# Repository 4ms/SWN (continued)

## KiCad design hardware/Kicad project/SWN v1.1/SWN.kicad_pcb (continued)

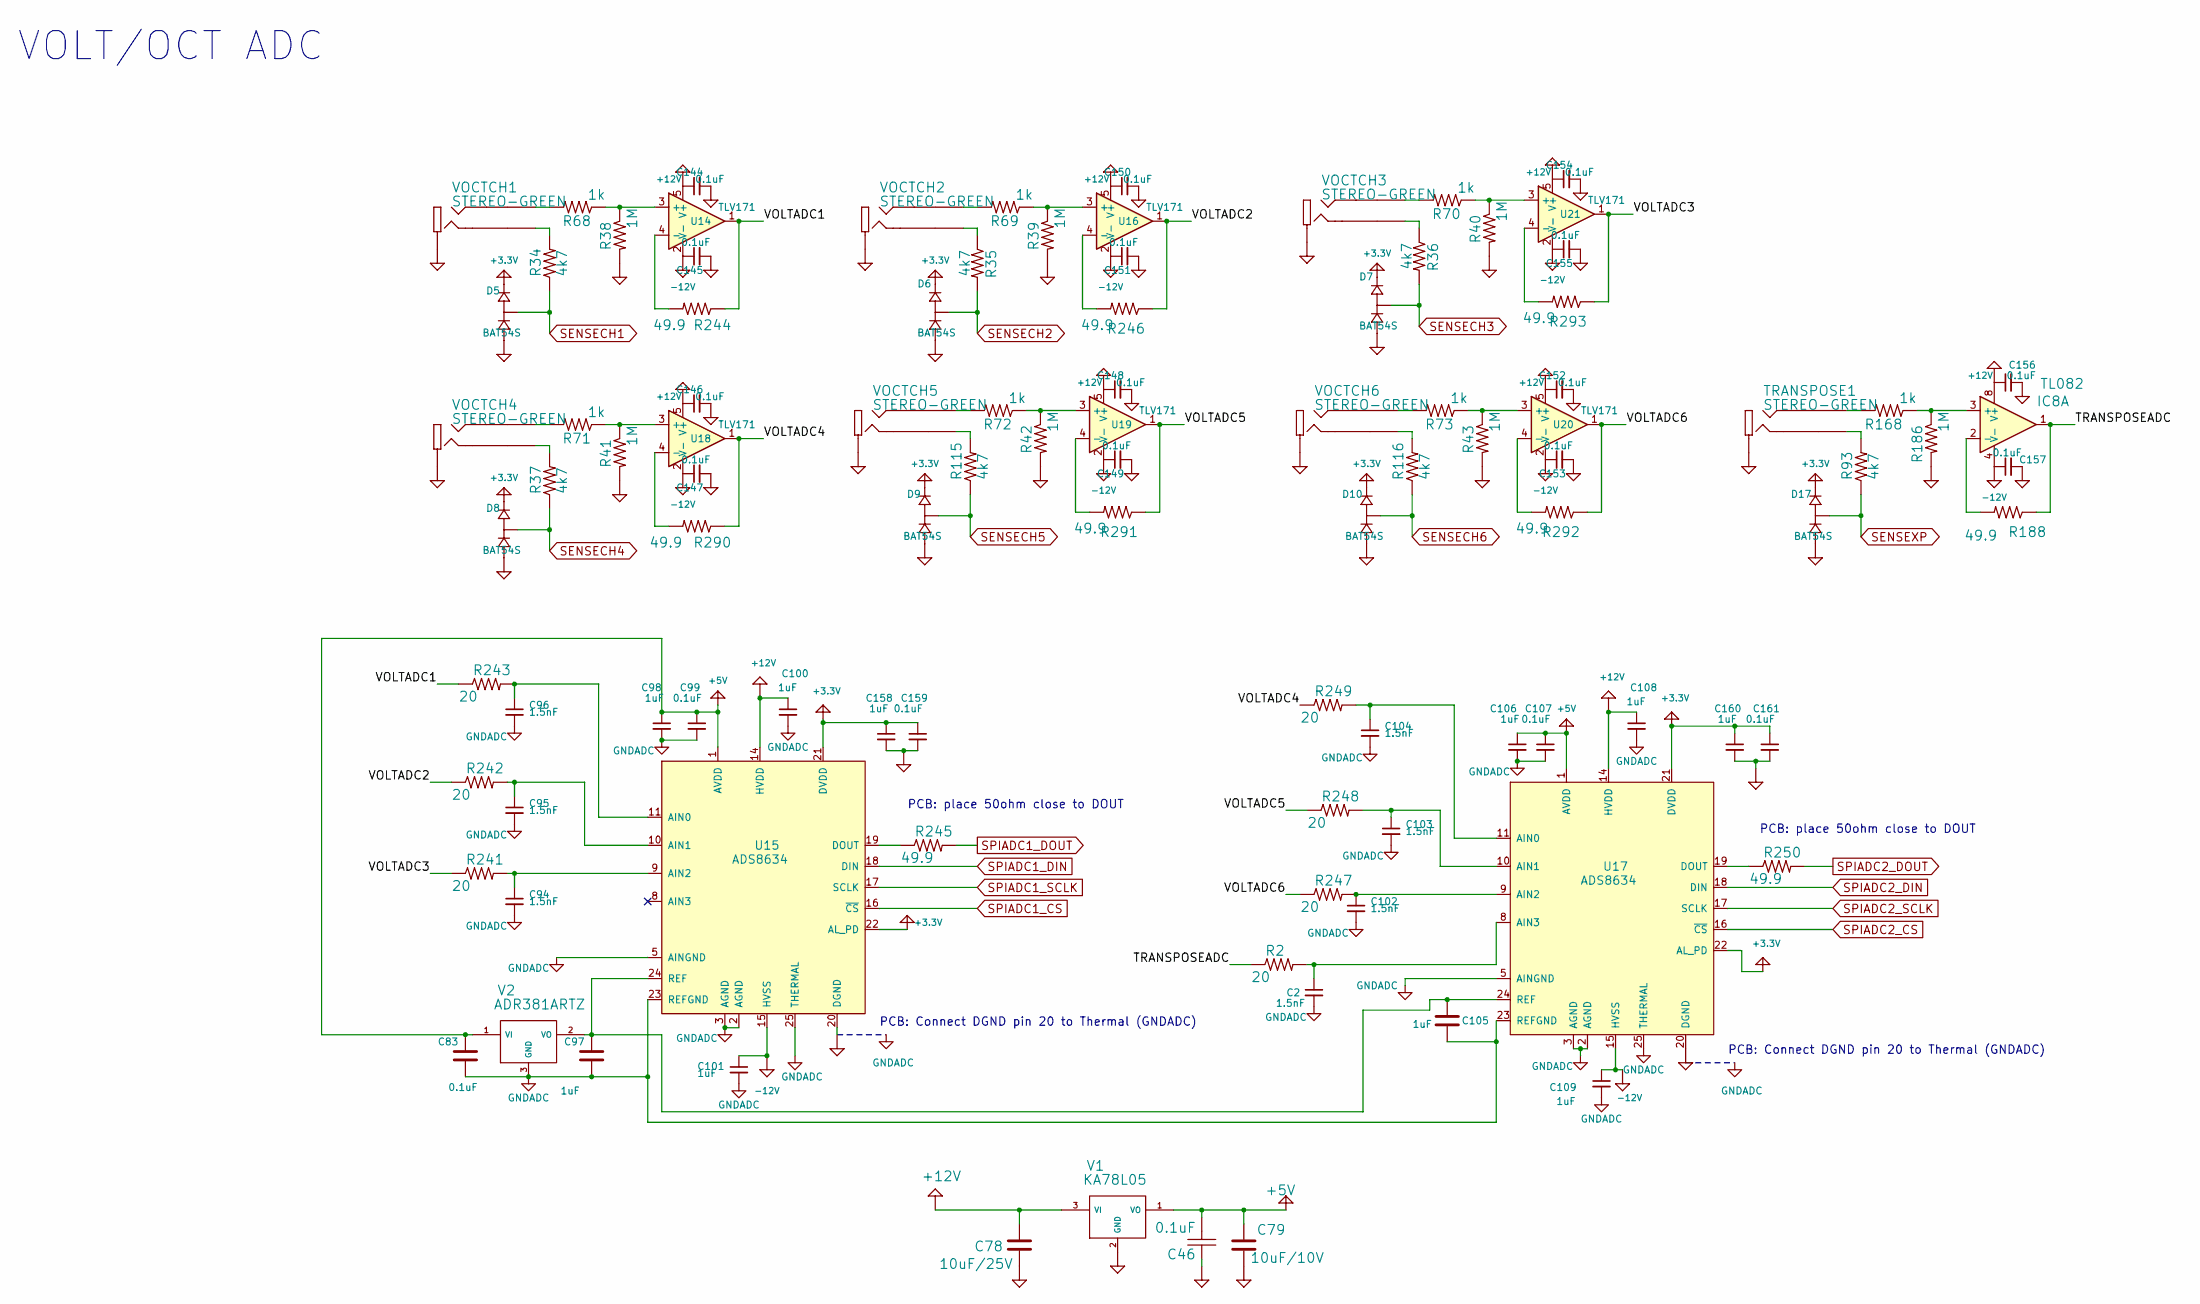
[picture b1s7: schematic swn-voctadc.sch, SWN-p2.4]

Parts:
C2, C94, C95, C96, C102, C103, C104: 1.5nF; C0603
C46, C83, C99, C107, C144, C145, C146, C147, C148, C149, C150, C151, C152, C153, C154, C155, C156, C157, C159, C161: 0.1uF; C0603
C78: 10uF/25V; C1206
C79: 10uF/10V; C0603
C97, C98, C100, C101, C105, C106, C108, C109, C158, C160: 1uF; C0603
D5, D6, D7, D8, D9, D10, D17: BAT54S; SOT23
IC8: TL082; TSSOP-8_4.4x3mm_Pitch0.65mm
R2, R241, R242, R243, R247, R248, R249: 20; R0603
R34, R35, R36, R37, R93, R115, R116: 4k7; R0603
R38, R39, R40, R41, R42, R43, R186: 1M; R0603
R68, R69, R70, R71, R72, R73, R168: 1k; R0603
R188, R244, R245, R246, R250, R290, R291, R292, R293: 49.9; R0603
TRANSPOSE1: STEREO-GREEN; PJ301M-12
U14, U16, U18, U19, U20, U21: TLV171; SOT-23-5
U15, U17: ADS8634; QFN-24-1EP_4x4mm_Pitch0.5mm
V1: KA78L05; SOT-89-3
V2: ADR381ARTZ; SOT23-3_PO132
VOCTCH1, VOCTCH2, VOCTCH3, VOCTCH4, VOCTCH5, VOCTCH6: STEREO-GREEN; PJ301M-12

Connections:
+3.3V: C158.1, C159.1, C160.1, C161.1, D5.2 (CATHODE), D6.2 (CATHODE), D7.2 (CATHODE), D8.2 (CATHODE), D9.2 (CATHODE), D10.2 (CATHODE), D17.2 (CATHODE), U15.21 (DVDD), U15.22 (AL_PD), U17.21 (DVDD), U17.22 (AL_PD); also elsewhere on the board
+5V: C46.2, C79.2, C83.1, C98.1, C99.1, C106.1, C107.1, U15.1 (AVDD), U17.1 (AVDD), V1.1 (VO), V2.1 (VI)
+12V: C78.1, C100.1, C108.1, C144.1, C146.1, C148.1, C150.1, C152.1, C154.1, C156.1, IC8.8 (V+), U14.5 (V+), U15.14 (HVDD), U16.5 (V+), U17.14 (HVDD), U18.5 (V+), U19.5 (V+), U20.5 (V+), U21.5 (V+), V1.3 (VI); also elsewhere on the board
-12V: C101.1, C109.1, C145.1, C147.1, C149.1, C151.1, C153.1, C155.1, C157.1, IC8.4 (V-), U14.2 (V-), U15.15 (HVSS), U16.2 (V-), U17.15 (HVSS), U18.2 (V-), U19.2 (V-), U20.2 (V-), U21.2 (V-); also elsewhere on the board
/V/OCT ADC/TRANSPOSEADC: IC8.1, R2.1, R188.1
/V/OCT ADC/VOLTADC1: R243.1, R244.1, U14.1
/V/OCT ADC/VOLTADC2: R242.1, R246.1, U16.1
/V/OCT ADC/VOLTADC3: R241.1, R293.1, U21.1
/V/OCT ADC/VOLTADC4: R249.1, R290.1, U18.1
/V/OCT ADC/VOLTADC5: R248.1, R291.1, U19.1
/V/OCT ADC/VOLTADC6: R247.1, R292.1, U20.1
GNDADC: C2.2, C83.2, C94.2, C95.2, C96.2, C97.2, C98.2, C99.2, C100.2, C101.2, C102.2, C103.2, C104.2, C105.2, C106.2, C107.2, C108.2, C109.2, U15.2 (AGND), U15.3 (AGND), U15.5 (AINGND), U15.23 (REFGND), U15.25 (THERMAL), U17.2 (AGND), U17.3 (AGND), U17.5 (AINGND), U17.23 (REFGND), U17.25 (THERMAL), V2.3 (GND); also elsewhere on the board
unnamed: C2.1, R2.2, U17.8 (AIN3)
unnamed: C94.1, R241.2, U15.9 (AIN2)
unnamed: C95.1, R242.2, U15.10 (AIN1)
unnamed: C96.1, R243.2, U15.11 (AIN0)
unnamed: C102.1, R247.2, U17.9 (AIN2)
unnamed: C103.1, R248.2, U17.10 (AIN1)
unnamed: C104.1, R249.2, U17.11 (AIN0)
unnamed: C97.1, C105.1, U15.24 (REF), U17.24 (REF), V2.2 (VO)
unnamed: IC8.2 (-), R188.2
unnamed: IC8.3 (+), R168.1, R186.1
unnamed: R34.2, VOCTCH1.3 (TIP-SW)
unnamed: R35.1, VOCTCH2.3 (TIP-SW)
unnamed: R36.1, VOCTCH3.3 (TIP-SW)
unnamed: R37.2, VOCTCH4.3 (TIP-SW)
unnamed: R38.1, R68.1, U14.3 (+)
unnamed: R39.1, R69.1, U16.3 (+)
unnamed: R40.1, R70.1, U21.3 (+)
unnamed: R41.1, R71.1, U18.3 (+)
unnamed: R42.1, R72.1, U19.3 (+)
unnamed: R43.1, R73.1, U20.3 (+)
unnamed: R68.2, VOCTCH1.1 (TIP)
unnamed: R69.2, VOCTCH2.1 (TIP)
unnamed: R70.2, VOCTCH3.1 (TIP)
unnamed: R71.2, VOCTCH4.1 (TIP)
unnamed: R72.2, VOCTCH5.1 (TIP)
unnamed: R73.2, VOCTCH6.1 (TIP)
unnamed: R93.2, TRANSPOSE1.3 (TIP-SW)
unnamed: R115.2, VOCTCH5.3 (TIP-SW)
unnamed: R116.2, VOCTCH6.3 (TIP-SW)
unnamed: R168.2, TRANSPOSE1.1 (TIP)
unnamed: R244.2, U14.4 (-)
unnamed: R245.1, U15.19 (DOUT)
unnamed: R246.2, U16.4 (-)
unnamed: R250.1, U17.19 (DOUT)
unnamed: R290.2, U18.4 (-)
unnamed: R291.2, U19.4 (-)
unnamed: R292.2, U20.4 (-)
unnamed: R293.2, U21.4 (-)
SENSECH1: D5.3 (COMMON), R34.1; also elsewhere on the board
SENSECH2: D6.3 (COMMON), R35.2; also elsewhere on the board
SENSECH3: D7.3 (COMMON), R36.2; also elsewhere on the board
SENSECH4: D8.3 (COMMON), R37.1; also elsewhere on the board
SENSECH5: D9.3 (COMMON), R115.1; also elsewhere on the board
SENSECH6: D10.3 (COMMON), R116.1; also elsewhere on the board
SENSEXP: D17.3 (COMMON), R93.1; also elsewhere on the board
SPIADC1_CS: U15.16 (~CS); also elsewhere on the board
SPIADC1_DIN: U15.18 (DIN); also elsewhere on the board
SPIADC1_DOUT: R245.2; also elsewhere on the board
SPIADC1_SCLK: U15.17 (SCLK); also elsewhere on the board
SPIADC2_CS: U17.16 (~CS); also elsewhere on the board
SPIADC2_DIN: U17.18 (DIN); also elsewhere on the board
SPIADC2_DOUT: R250.2; also elsewhere on the board
SPIADC2_SCLK: U17.17 (SCLK); also elsewhere on the board

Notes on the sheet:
VOLT/OCT ADC
PCB: place 50ohm close to DOUT
PCB: Connect DGND pin 20 to Thermal (GNDADC)

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
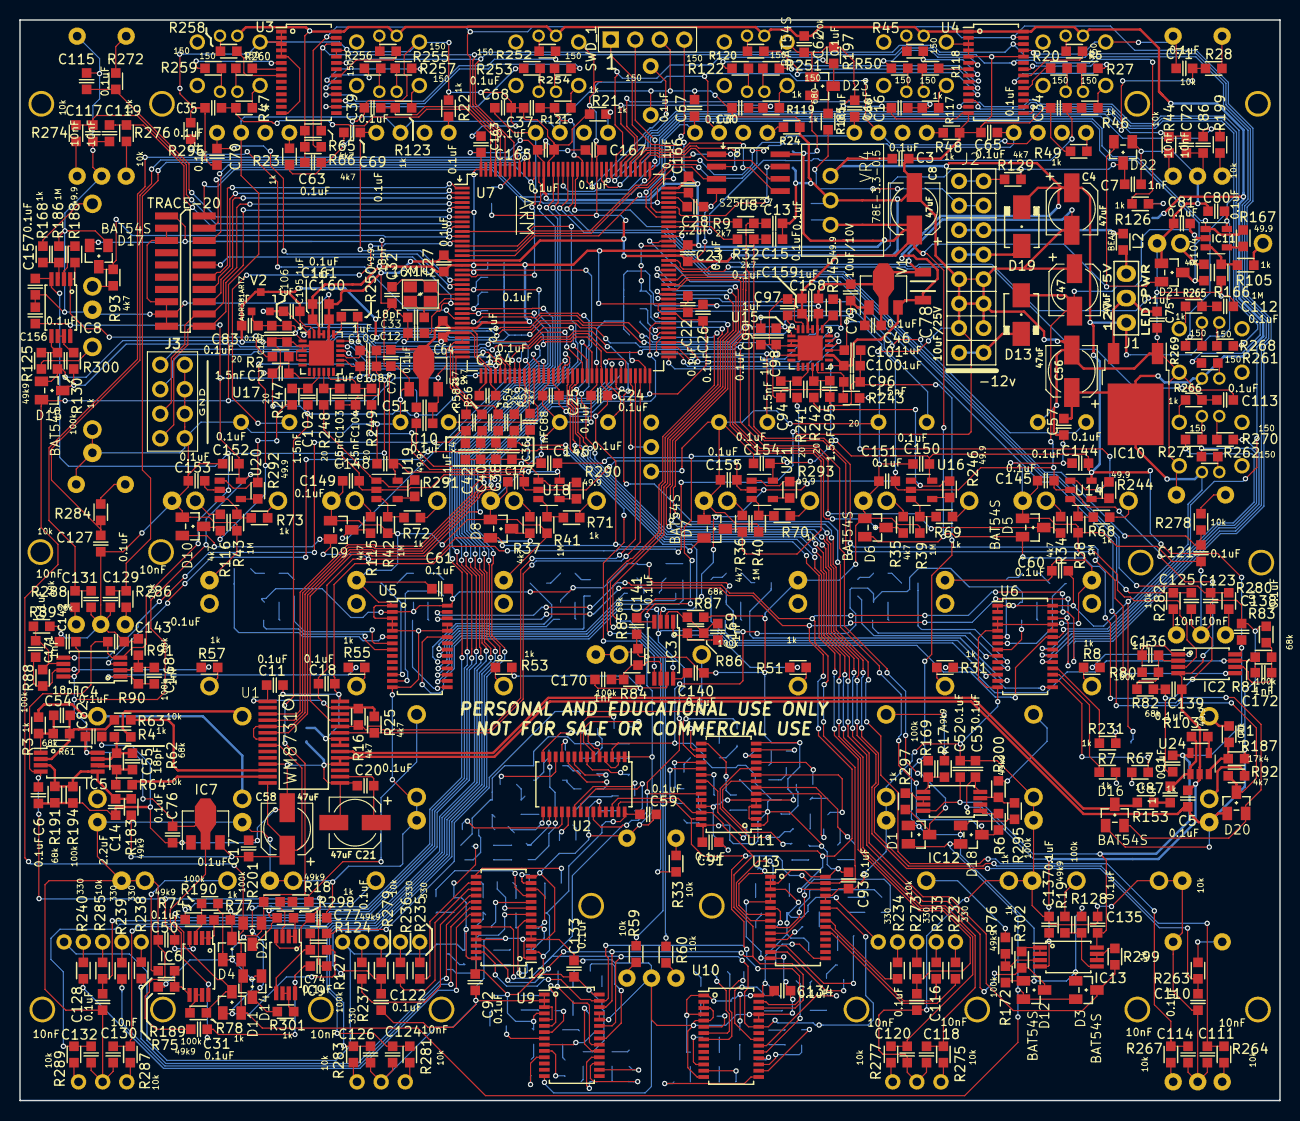
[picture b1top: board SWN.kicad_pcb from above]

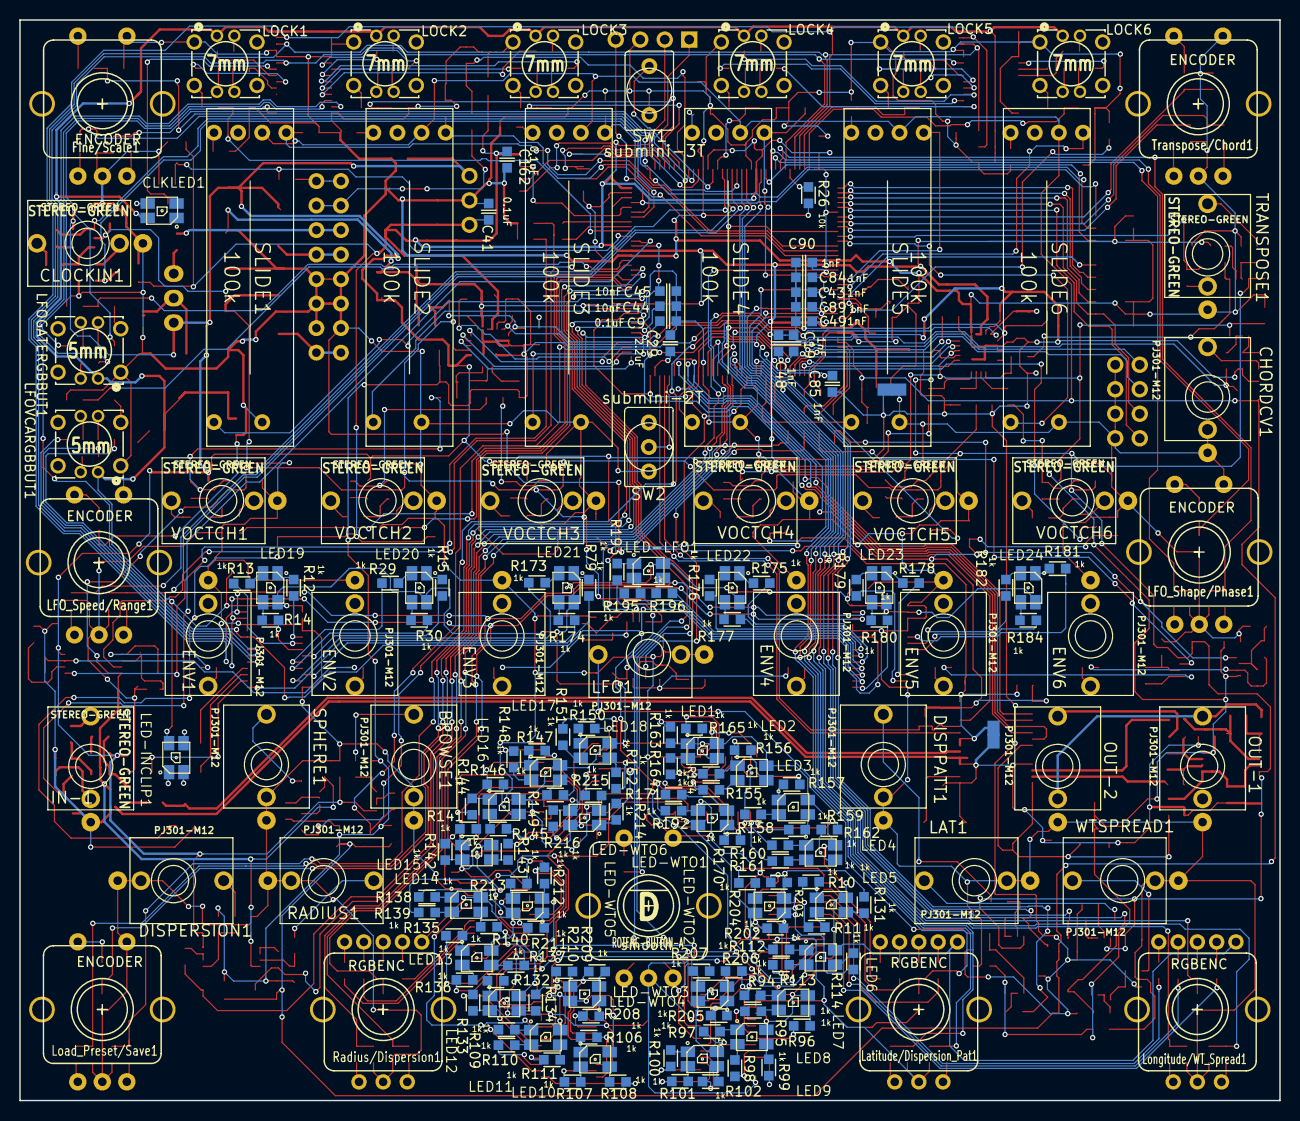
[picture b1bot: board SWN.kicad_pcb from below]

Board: 2 copper layers, 130.6 x 112.0 mm, 614 parts (196 on the bottom side), 552 nets.

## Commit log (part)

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2019-05-17 First public commit
2019-05-18 Updated LICENSE, README, and removed 4ms logos from PCB
2019-05-18 README updated
2019-05-20 Level is linearly interpolated between codec blocks to prevent zippering
2019-05-20 Fixed wraparound distortion on waveform input when recording
2019-05-20 Fixed issue where loading a preset containing a scale would not refresh the channel pitches
2019-05-20 Transpose display shows mutes on buttons. Shorter timeout for display
2019-05-20 Fixed display of non-detuned channels
2019-05-20 WT Rec mode starts at 0,0,0 to avoid confusion with browsing a recording
    Browsing with a non-zero lat/long/depth will be a totally different pattern, so the waveforms will seem "out of order"
2019-05-20 Fixed LED brightness not properly showing wt_pos in WT_EDIT mode
2019-05-20 Analog conditioning and hires ADC read is faster to prevent zippering
2019-05-20 Added Change Log
2019-07-12 External ADC runs purely on interrupt instead of dedicated timer
2019-07-12 Removed remnants of old timer for external ADCs
2019-07-12 Trimming octaves like transpose is down (not tested on hardware)
2019-07-12 Octave parameter is clamped to active range (0-MAXOCT) and spacing is preserved
    Enforcing a hard clamp of -MAX_OCT to MAX_OCT*2 so
2019-07-12 Dim octave positions inactive
2019-07-12 Extended octave range: -3 to 14
2019-07-12 LED display for octave tweaked
2019-07-12 Using the same timer for all lock flashing
2019-07-12 Allowing Locks
2019-07-12 New display: Sphere Selection
    Displays wt_sel on buttons and outer ring as a sphere is selected or WT Spread is applied. Tapping center rotary enables the display
2019-07-12 Using common function for rotating led ring origin
2019-07-12 Cleaned up encoder led color logic: now they are always orange in WT REC mode
2019-07-12 Sphere Selection lights skip blank spheres, but still use the actual color
2019-07-12 Fixed FX display in WT EDIT mode (push and turn on rotary went to spheresel)
2019-07-12 Locks display in proper spot on led ring
    Massive whitespace cleanup on led_cont
2019-07-12 Whitespace and readability changes
    Nothing the compiler will care about
2019-07-12 Renamed constant for clarity
2019-07-12 WIP setting up DMA for I2C of PCA chips
2019-07-12 Add Play Export feature: tap Browse in WTEDIT mode
    Plays each wt in sphere 8x, in the browse order. Light ring animation is timed to playback.
2019-07-12 Updated HAL I2C to latest, trying to get DMA to show that it's ready after xmit
2019-07-12 WIP: DMA of I2C
2019-07-12 Comments in makefile
2019-07-12 Higher priority to I2C EV IRQ fixed timeout from ext flash spi interrupting it.
    Also found double buffer to be unneccessary and removed. And fixed bug in single LED set function
2019-07-12 Implemented double buffer, not sure if it's needed. I2C DMA works but seems to be colliding with extflash reads
2019-07-12 WIP with SPI DMA
2019-07-12 removed unused CODEC RESET pin defs (conflict with SPI FLASH pin)
2019-07-12 SPI Flash can read on DMA
2019-07-12 Separated SPIDMA functions from non-DMA SPI, and from chip specific defs
2019-07-12 Fixed issue where only first channel would update wt_bank
2019-07-12 Fixed issue with only first channel loading wt from flash
2019-07-12 Preset writes/reads to flash using DMA-friendly memory
2019-07-12 Working on tests
2019-07-12 Tests for flash writing (WIP)
2019-07-12 WT Browsing slowed down now that tables load so much faster
2019-07-12 Flash writing writes sizes greater than page size, and non-page-aligned data, too.
2019-07-12 Using DMA-friendly memory for writing spheres. WIP: Broken!
2019-07-12 Spherebuf can be saved without huge temporary memory structure
2019-07-12 Play Export uses rendered sphere, instead of ext flash.
    Previously, FX were not exported
2019-07-12 Dispersion pattern not cleared when exiting WT REC
2019-07-12 Higher threshold for starting recording, and skips first half-WT_TABLELEN
2019-07-12 Play Export starts from monitoring mode (which forces silence at the start of the export)
2019-07-12 Fixed bug where WTEDIT would not refresh waveform at 0,0,0
2019-07-12 Play Export audio buffer callback placed in own function
2019-07-12 Disable/Enable Spheres. Clear/Unclear Spheres. Load Sphere in WTREC
    Disabled/Enabled spheres is saved in Preset. Cleared spheres can be uncleared until power down.
2019-07-12 Wavetable_saving renamed to wavetable_saveload
2019-07-12 Fixed SPI DMA collision when loading a preset while browsing
2019-07-12 Can record one waveform with Fine+Record
2019-07-12 Can lock/unlock in key/note mode
2019-07-12 lfo.mode, lfo.to_vca, key mode can be individually set for locked channels
2019-07-12 Sphere Selection displays better on buttons in note/key mode
    Also reverted a change so that now sphere sel and wtpos can be changed for locked channels using channel button
2019-07-12 Removed unused constants
2019-07-12 Tweaked browse and wt xfade timing
2019-07-12 Key combo change: Pset+Dep+Lat = reset Nav; Pset+Long = reset wt sel
    ...
2019-07-12 LFO CV bug fixed (high then low CV would break LFO speed)
2019-07-12 Better idea: Pset+Depth = reset nav; Pset+Lat = reset sphere sel
    The v1 key combo (Pset+Depth+Lat) still works to reset nav and sphere sel.
2019-07-12 Updated changelog
2019-07-12 WT Spread spreads evenly on all channels (center-outwards), rather than with a LUT
2019-07-12 Bumped version to 1.2, and updated Changelog
2019-07-12 LFO Phase changes by 1/24, not by a LUT
2019-07-12 External Trig mode: New Key Switch mode uses CV jacks for triggers to fire envelopes
    In the process of adding, finished removing extra monitor code from oscillator main codec processing
2019-07-12 Allow Note Mode envelopes to be very short
    Running your finger up a scale on a CV keyboard now triggers every note
2019-07-12 Key Sw mode colors set individually, not by order in palette
2019-07-12 Removed support for PCB_VERSION <= 23
2019-07-12 Disable quantization lockout period for new Key Sw mode
2019-07-12 Finished removing support for PCB_VERSION <= 23
2019-07-12 Using raw ADC for CV jack gate detection allows for detecting thinner pulses
2019-07-12 Force update of WT on entering EXT TRIG mode to clear any offset from CV
2019-07-12 Track pitch in EXT TRIG mode so we're more accurate to the CV source
    Otherwise if there's slew or noise we might latch a bad value for pitch
2019-07-12 Some debugging flags (disabled, but handy for testing)
2019-07-12 Bumped to v1.3 and updated CHANGELOG
2019-07-12 Fixed CV effecting locked channels.
2019-07-12 Ext Trig mode: Spread CV acts as global trigger when Transpose CV jack is plugged
    Other trig jacks resume normal function if associated Voct jack is unplugged
2019-07-12 Partially reverted using main audio callback for some WT modes
2019-07-12 Fixed missing note in semitones scale
2019-07-12 Calibrate Voct mode turns off LFO to VCA, unmutes all and enters mute mode
2019-07-12 Comments and todos
2019-07-12 Remove DC offset (average around zero) when play exporting
2019-07-12 Switching to CV/Gate goes to unquantized scale
2019-07-12 Switching to Mute mode goes to Semitones, not Major scale.
2019-07-12 Ignore presets from earlier than v1.0
2019-07-12 version bumped up to 2.0
2019-07-12 Fixed bug with Locks toggling when adjusting a channel's fine params
    Mute mode: lock would toggle if unmuting/muting after adjusting a channel button+fine+knob
    Other modes: lock would toggle immediately
2019-07-12 Updated v2.0 CHANGELOG
2019-07-12 Allow en/disable sphere after Preset knob is tapped to load
2019-07-12 Better color constrast for factory spheres (more blue)
2019-07-12 WTSEL has even spacing, not a LUT (Re-commited accidentally reverted commit)
2019-07-12 Credit where credit is due
2019-07-12 Turned off Debug pin output
2019-07-12 LFO CV works in Note/Key/CVGate modes
2019-07-15 Spread knob wrapped improperly when going from 0 to -1
    Was skipping last chord
2019-07-15 Chord list fixed: minor 3rd, minor and major 9th and 11th had some wrong notes
2019-07-15 make release asks for version number and zips up wav file
2019-07-15 Spread CV responds to black keys C#0 to C#5 to pick chords
2019-07-15 Updated CHANGELOG for v2.1 features so far
2019-07-16 Fixed Chord 6, from sus4 to M3. Bumped to v2.1
2019-09-05 Updated bootloader with correct name of non-DMA LED init function
2019-09-05 Schematic symbol library alias created for F765 chip
    Symbol changed to F765 in schematic
2019-09-05 Schematic updated to use KiCad 5.1.4 and new 4ms-vreg library.
2019-09-06 Hardware test procedure added
2020-05-28 Spheres are loaded after hardware test, before boot.
    Reduces risk of power-cycling corrupting a flash load.
    On boot, if a factory sphere is detected as missing, it's reloaded
2020-05-28 Makefile cleanup
2020-05-28 Guards against null pointer if spheres are not included in build
2020-05-29 Sources are built in sorted order, and ld uses --start-group. Fixes runtime error with some gcc versions (9.2)
2020-05-29 Updated README to include latest tools and Virtual Machine
2020-05-29 make wav set pythonpath before running
2020-09-16 Sliders flicker when using cached level (after panning)
2020-09-16 Added .clang-format file to project
2020-09-16 Updated clang_format
2020-09-16 Reverting an #include that was accidentally added
2020-09-16 Fixed deprecated use of sp clobbering
    set_MSP was clobbering stack pointer, which is no longer allowed in gcc >9.1.
2020-09-16 Linking into FLASHITCM instead of AXI
    Fixes issue with gcc 9 loading bad data from FLASH (const variables)
2020-09-16 Linking into AXI flash, not using ITCM anywhere. Enabled I Cache.
2020-09-16 Stubs for setting startup preset
2020-09-16 Added persistant_storage.hh
2020-09-16 Constants for startup preset sector
2020-09-16 Fixed collision on flash if WT and startup preset save access at same time
2020-09-16 Startup preset stored in sFLASH sector using write-leveling
2020-09-16 Simplified how to perform a preset store and recall
    Moved setting the hover_num and the animation start into the store/recall functions
2020-09-16 Added SelBus enable/disable of recall and save to system Settings
2020-09-16 Changed startup preset sFLASH sector
2020-09-16 Added SelBus toggle display, and key combos
2020-09-16 Buttons in CV/Gate/Sus mode can sustain, just like jacks
    Fixed bug where Sphere CV jack didn't work in CV/Gate mode
2020-09-16 Fixed issue where Preset knob didn't ever display
    And preset mode exits if selbus key combos detected
2020-09-16 Bumped version to v2.2
2020-09-16 Explicitly use python2 to `make wav`
2020-09-25 Selbus only captures first 2 data bytes after a command
2020-09-25 Selbus ignores MakeNoise "Store All" command
2020-09-25 Selbus properly displays preset number on light ring when saving
2020-10-12 Updated CHANGELOG to v2.2
2021-01-25 4k7 -> 10k for global control schematic resistors
    There's a disparity between the resistors in these positions between the schematic and the PCB. I cross referenced this against the product photos on the 4ms website and it appears as though the PCB 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
2021-05-07 Reverting back to ITCM, and disabling ICache
2021-05-07 Fix: deleted user sphere still can be selected (as blank) until reboot
2021-05-07 Can force factory spheres to re-load on boot
2021-05-07 updated CHANGELOG with bug fix
2021-05-07 bootloader linker script ensures binary doesn't spill into app sector
2021-05-07 Fixed fine-tuning not applying immediately when preset is loaded.
2022-01-25 Removed unnecessary linker flag
    --start-group is not needed
2022-01-25 Fixes #3: hangs when run after compiling with arm-none-eabi-gcc v7.3.1
    Debugging showed that const data (in the .rodata section) was corrupted. Data that should be found at a particular address was actually four bytes prior. The DMA init in `DMA_CalcBaseAndBitshift()` w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
    The problem was that the linker script allowed the LMA and VMA counters to get out of sync. Adding the ALIGN_WITH_INPUT flag fixed this. See: https://sourceware.org/binutils/docs-2.35/ld/Forced-Outpu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
2022-01-27 all linker output sections that have different LMA/VMA need to have ALIGN_WITH_INPUT attribute
